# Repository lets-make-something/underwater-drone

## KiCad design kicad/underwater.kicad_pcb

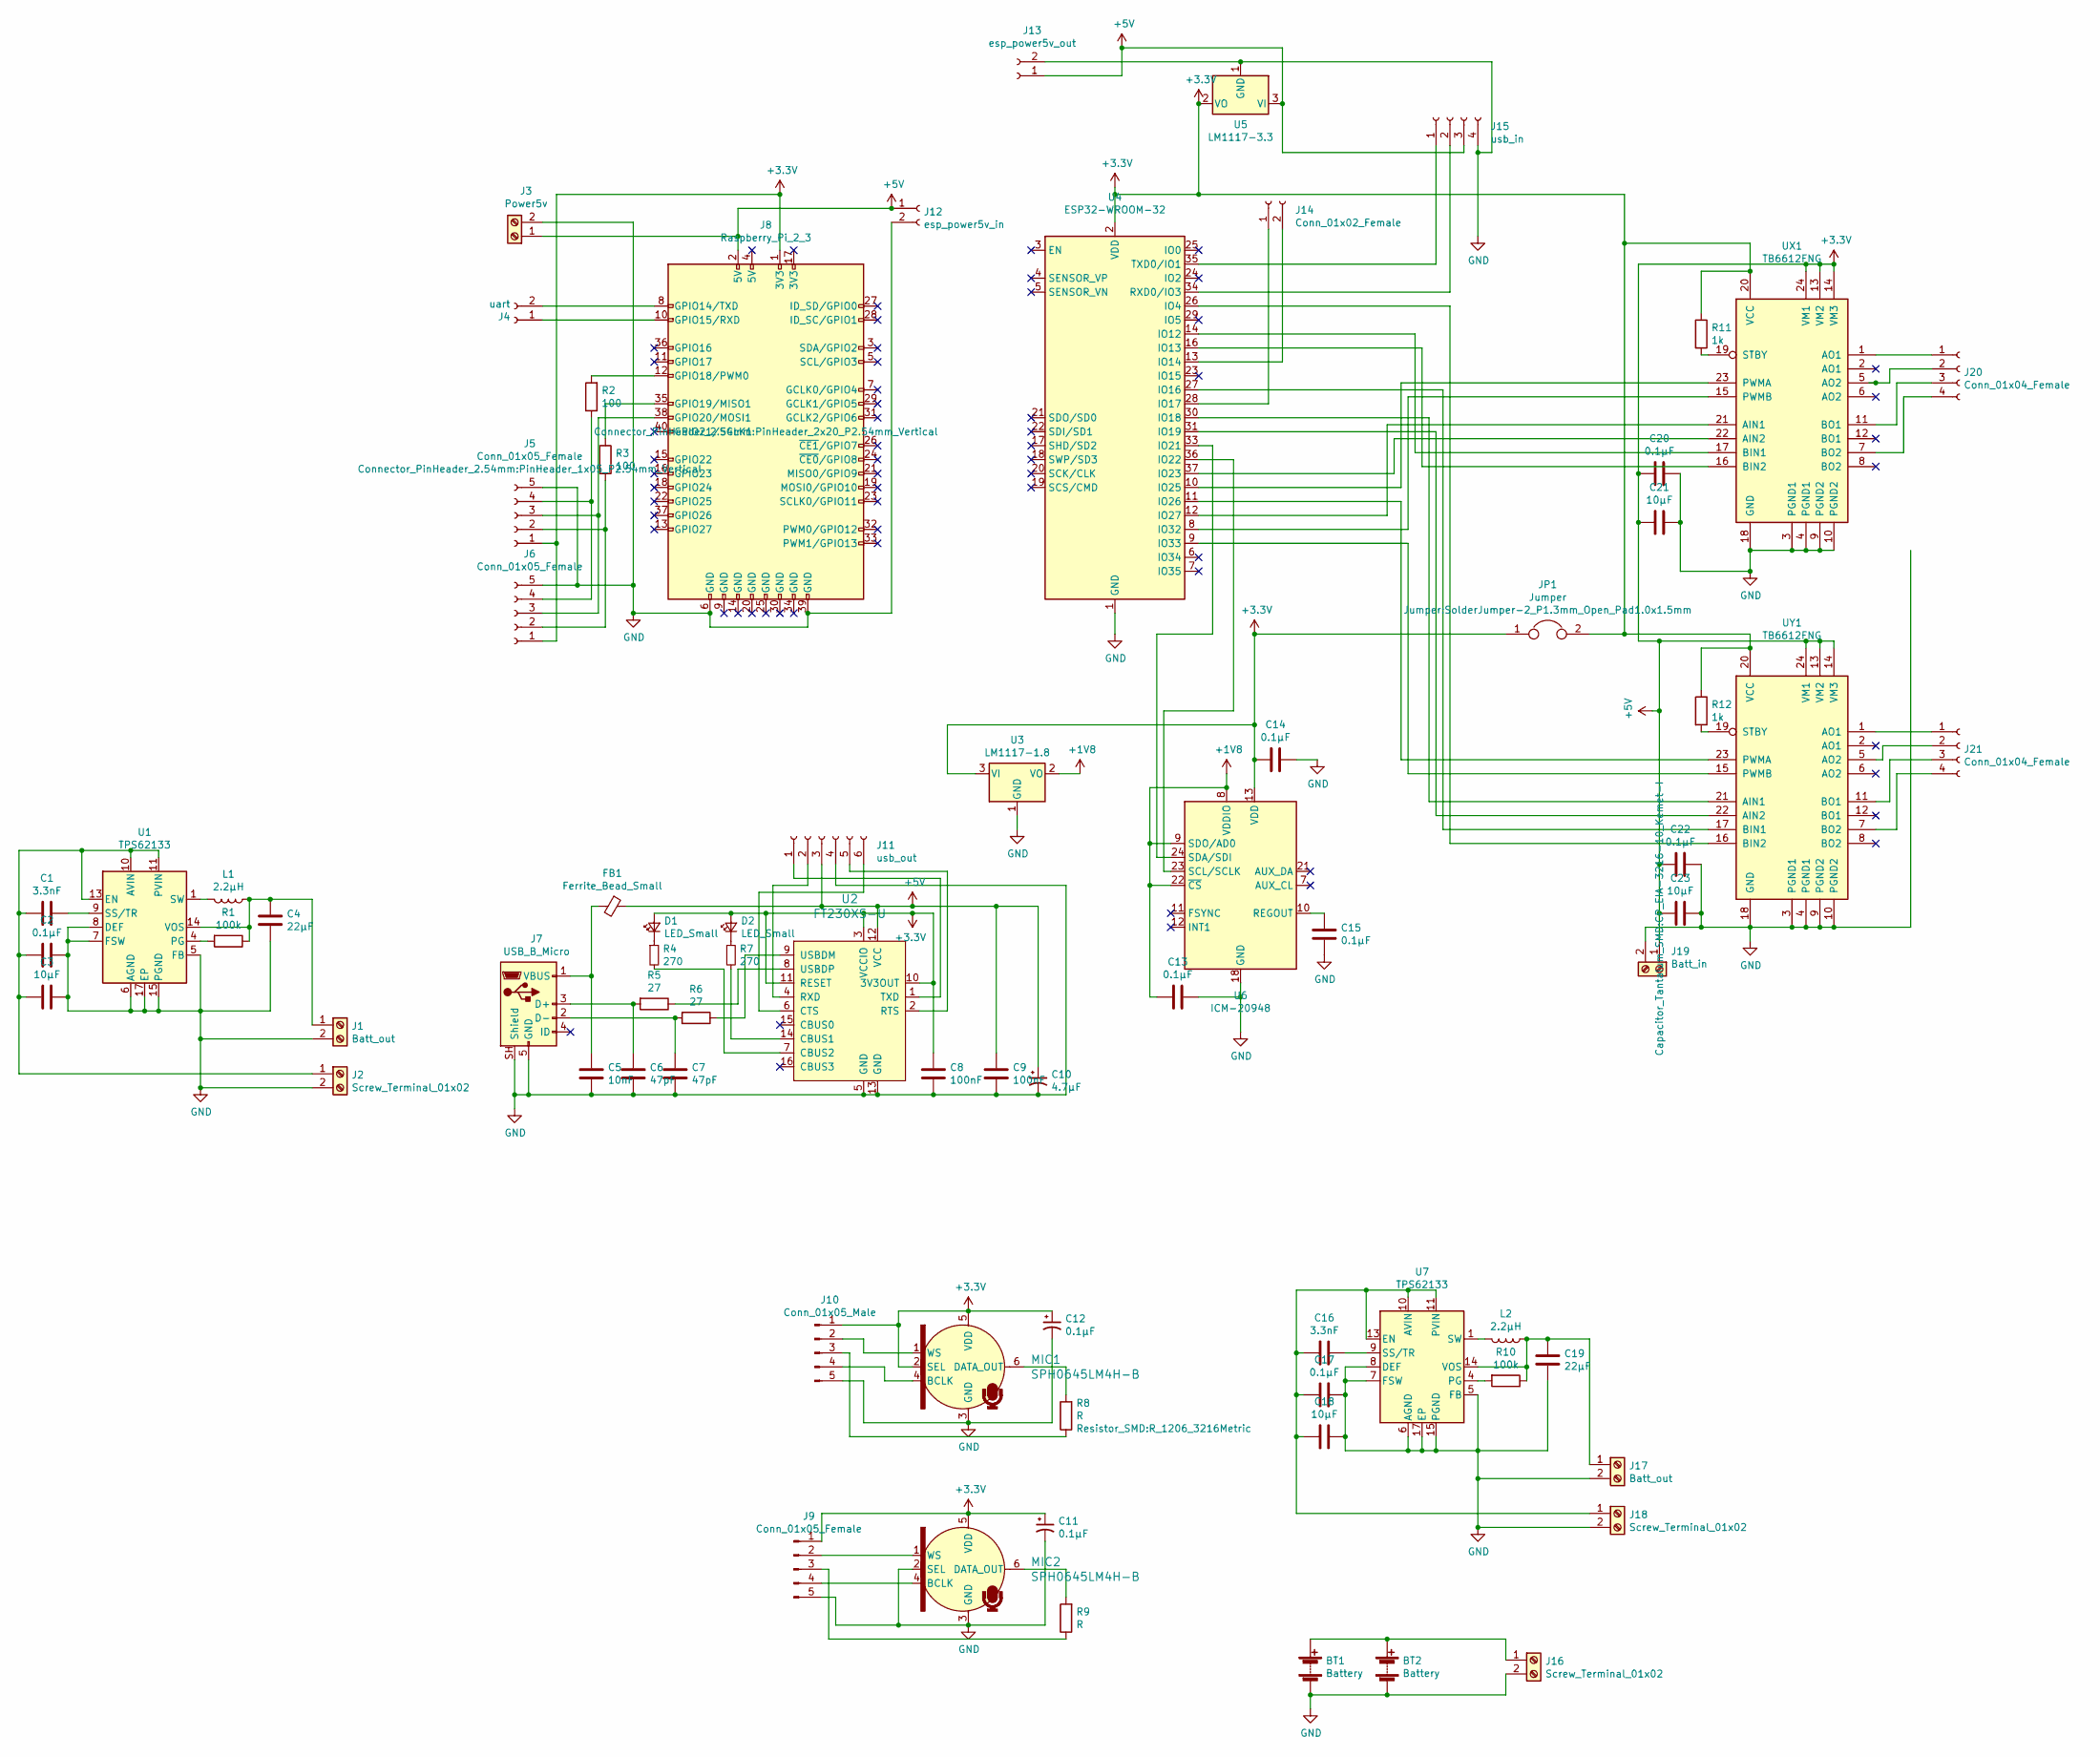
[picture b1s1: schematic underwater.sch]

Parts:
BT1, BT2: Battery; BatteryHolder_Keystone_1042_1x18650
C1, C16: 3.3nF; C_1206_3216Metric
C2, C13, C14, C15, C17, C20, C22: 0.1μF; C_1206_3216Metric
C3, C18, C21, C23: 10μF; CP_EIA-3216-10_Kemet-I
C4, C19: 22μF; CP_EIA-3216-10_Kemet-I
C5: 10nF; C_1206_3216Metric
C6, C7: 47pF; C_1206_3216Metric
C8, C9: 100nF; C_1206_3216Metric
C10: 4.7μF; CP_EIA-3216-10_Kemet-I
C11, C12: 0.1μF; CP_EIA-3216-10_Kemet-I
D1, D2: LED_Small; LED_1206_3216Metric
FB1: Ferrite_Bead_Small; 1206
J1, J17: Batt_out; TerminalBlock_bornier-2_P5.08mm
J2, J16, J18: Screw_Terminal_01x02; TerminalBlock_bornier-2_P5.08mm
J3: Power5v; TerminalBlock_bornier-2_P5.08mm
J4: uart; PinHeader_1x02_P2.54mm_Vertical
J5, J6, J9: Conn_01x05_Female; PinHeader_1x05_P2.54mm_Vertical
J7: USB_B_Micro; USB_Micro_B_Female_10118192
J8: Raspberry_Pi_2_3; PinHeader_2x20_P2.54mm_Vertical
J10: Conn_01x05_Male; PinHeader_1x05_P2.54mm_Vertical
J11: usb_out; PinHeader_1x06_P2.54mm_Vertical
J12: esp_power5v_in; PinHeader_1x02_P2.54mm_Vertical
J13: esp_power5v_out; PinHeader_1x02_P2.54mm_Vertical
J14: Conn_01x02_Female; PinHeader_1x02_P2.54mm_Vertical
J15: usb_in; PinHeader_1x04_P2.54mm_Vertical
J19: Batt_in; TerminalBlock_bornier-2_P5.08mm
J20, J21: Conn_01x04_Female; PinHeader_1x04_P2.54mm_Horizontal
JP1: Jumper; SolderJumper-2_P1.3mm_Open_Pad1.0x1.5mm
L1, L2: 2.2μH; L_1206_3216Metric
MIC1, MIC2: SPH0645LM4H-B; MPN SPH0645LM4H-B; Digi-Key_PN 423-1405-1-ND
R1, R10: 100k; R_1206_3216Metric
R2, R3: 100; R_1206_3216Metric
R4, R7: 270; R_1206_3216Metric
R5, R6: 27; R_1206_3216Metric
R8, R9: R; R_1206_3216Metric
R11, R12: 1k; R_1206_3216Metric
U1, U7: TPS62133; VQFN-16-1EP_3x3mm_P0.5mm_EP1.68x1.68mm_ThermalVias
U2: FT230XS-U; SSOP-16_W3.90mm; MPN FT230XS-U; Digi-Key_PN 768-1154-5-ND
U3: LM1117-1.8; SOT-223-4
U4: ESP32-WROOM-32
U5: LM1117-3.3; SOT-223-4
U6: ICM-20948; InvenSense_QFN-24_3x3mm_P0.4mm
UX1: TB6612FNG; SSOP-24_5.3x8.2mm_P0.65mm
UY1: TB6612FNG; SSOP-24_5.3x8.2mm_P0.65mm

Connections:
+1V8: C13.2, U3.2 (VO), U6.8 (VDDIO), U6.9 (SDO/AD0), U6.22 (~CS)
+3V3: C8.1, C9.1, C10.1, C11.1, C12.1, C14.2, C20.2, C21.2, C22.2, C23.2, D1.2 (A), D2.2 (A), FB1.1, J3.1, J5.1, J6.1, J8.1 (3V3), J8.2 (5V), J9.1, J10.1, J11.3, J12.1, J13.1, J15.3, J19.1, JP1.1, JP1.2, MIC1.2 (SEL), MIC1.5 (VDD), MIC2.5 (VDD), R11.1, R12.1, U2.3 (VCCIO), U2.10 (3V3OUT), U2.11 (RESET), U2.12 (VCC), U3.3 (VI), U4.2 (VDD), U5.2 (VO), U5.3 (VI), U6.13 (VDD), UX1.13 (VM2), UX1.14 (VM3), UX1.20 (VCC), UX1.24 (VM1), UY1.13 (VM2), UY1.14 (VM3), UY1.20 (VCC), UY1.24 (VM1)
GND: BT1.2 (-), BT2.2 (-), C2.2, C3.2, C4.2, C5.2, C6.2, C7.2, C8.2, C9.2, C10.2, C11.2, C12.2, C13.1, C14.1, C15.2, C17.2, C18.2, C19.2, C20.1, C21.1, C22.1, C23.1, J1.2, J2.2, J3.2, J5.5, J6.5, J7.5 (GND), J7.SH (Shield), J8.6 (GND), J8.39 (GND), J9.5, J10.5, J11.4, J12.2, J13.2, J15.4, J16.2, J17.2, J18.2, J19.2, MIC1.3 (GND), MIC2.2 (SEL), MIC2.3 (GND), U1.5 (FB), U1.6 (AGND), U1.7 (FSW), U1.8 (DEF), U1.15 (PGND), U1.16 (PGND), U1.17 (EP), U2.5 (GND), U2.13 (GND), U3.1 (GND), U4.1 (GND), U4.15 (GND), U4.38 (GND), U5.1 (GND), U6.18 (GND), U6.20 (GND), U7.5 (FB), U7.6 (AGND), U7.7 (FSW), U7.8 (DEF), U7.15 (PGND), U7.16 (PGND), U7.17 (EP), UX1.3 (PGND1), UX1.4 (PGND1), UX1.9 (PGND2), UX1.10 (PGND2), UX1.18 (GND), UY1.3 (PGND1), UY1.4 (PGND1), UY1.9 (PGND2), UY1.10 (PGND2), UY1.18 (GND)
unnamed: BT1.1 (+), BT2.1 (+), J16.1
unnamed: C1.1, U1.9 (SS/TR)
unnamed: C1.2, C2.1, C3.1, J2.1, U1.10 (AVIN), U1.11 (PVIN), U1.12 (PVIN), U1.13 (EN)
unnamed: C4.1, J1.1, L1.1, R1.1, U1.14 (VOS)
unnamed: C5.1, FB1.2, J7.1 (VBUS)
unnamed: C6.1, J7.3 (D+), R5.2
unnamed: C7.1, J7.2 (D-), R6.2
unnamed: C15.1, U6.10 (REGOUT)
unnamed: C16.1, U7.9 (SS/TR)
unnamed: C16.2, C17.1, C18.1, J18.1, U7.10 (AVIN), U7.11 (PVIN), U7.12 (PVIN), U7.13 (EN)
unnamed: C19.1, J17.1, L2.1, R10.1, U7.14 (VOS)
unnamed: D1.1 (K), R4.1
unnamed: D2.1 (K), R7.1
unnamed: J4.1, J8.10 (GPIO15/RXD)
unnamed: J4.2, J8.8 (GPIO14/TXD)
unnamed: J5.2, J6.2, R3.2
unnamed: J5.3, J6.3, J8.38 (GPIO20/MOSI1)
unnamed: J5.4, J6.4, R2.1
unnamed: J8.12 (GPIO18/PWM0), R2.2
unnamed: J8.35 (GPIO19/MISO1), R3.1
unnamed: J9.2, MIC2.1 (WS)
unnamed: J9.3, R9.1
unnamed: J9.4, MIC2.4 (BCLK)
unnamed: J10.2, MIC1.1 (WS)
unnamed: J10.3, R8.1
unnamed: J10.4, MIC1.4 (BCLK)
unnamed: J11.1, U2.1 (TXD)
unnamed: J11.2, U2.4 (RXD)
unnamed: J11.5, U2.2 (RTS)
unnamed: J11.6, U2.6 (CTS)
unnamed: J14.1, U4.28 (IO17)
unnamed: J14.2, U4.13 (IO14)
unnamed: J15.1, U4.35 (TXD0/IO1)
unnamed: J15.2, U4.34 (RXD0/IO3)
unnamed: J20.1, UX1.1 (AO1)
unnamed: J20.2, UX1.5 (AO2)
unnamed: J20.3, UX1.11 (BO1)
unnamed: J20.4, UX1.7 (BO2)
unnamed: J21.1, UY1.1 (AO1)
unnamed: J21.2, UY1.5 (AO2)
unnamed: J21.3, UY1.11 (BO1)
unnamed: J21.4, UY1.7 (BO2)
unnamed: L1.2, U1.1 (SW), U1.2 (SW), U1.3 (SW)
unnamed: L2.2, U7.1 (SW), U7.2 (SW), U7.3 (SW)
unnamed: MIC1.6 (DATA_OUT), R8.2
unnamed: MIC2.6 (DATA_OUT), R9.2
unnamed: R1.2, U1.4 (PG)
unnamed: R4.2, U2.7 (CBUS2)
unnamed: R5.1, U2.8 (USBDP)
unnamed: R6.1, U2.9 (USBDM)
unnamed: R7.2, U2.14 (CBUS1)
unnamed: R10.2, U7.4 (PG)
unnamed: R11.2, UX1.19 (STBY)
unnamed: R12.2, UY1.19 (STBY)
unnamed: U4.8 (IO32), UX1.15 (PWMB)
unnamed: U4.9 (IO33), UY1.15 (PWMB)
unnamed: U4.10 (IO25), UX1.23 (PWMA)
unnamed: U4.11 (IO26), UY1.23 (PWMA)
unnamed: U4.12 (IO27), UX1.21 (AIN1)
unnamed: U4.14 (IO12), UX1.17 (BIN1)
unnamed: U4.16 (IO13), UX1.16 (BIN2)
unnamed: U4.26 (IO4), UY1.16 (BIN2)
unnamed: U4.27 (IO16), UY1.17 (BIN1)
unnamed: U4.30 (IO18), UY1.21 (AIN1)
unnamed: U4.31 (IO19), UY1.22 (AIN2)
unnamed: U4.33 (IO21), U6.24 (SDA/SDI)
unnamed: U4.36 (IO22), U6.23 (SCL/SCLK)
unnamed: U4.37 (IO23), UX1.22 (AIN2)

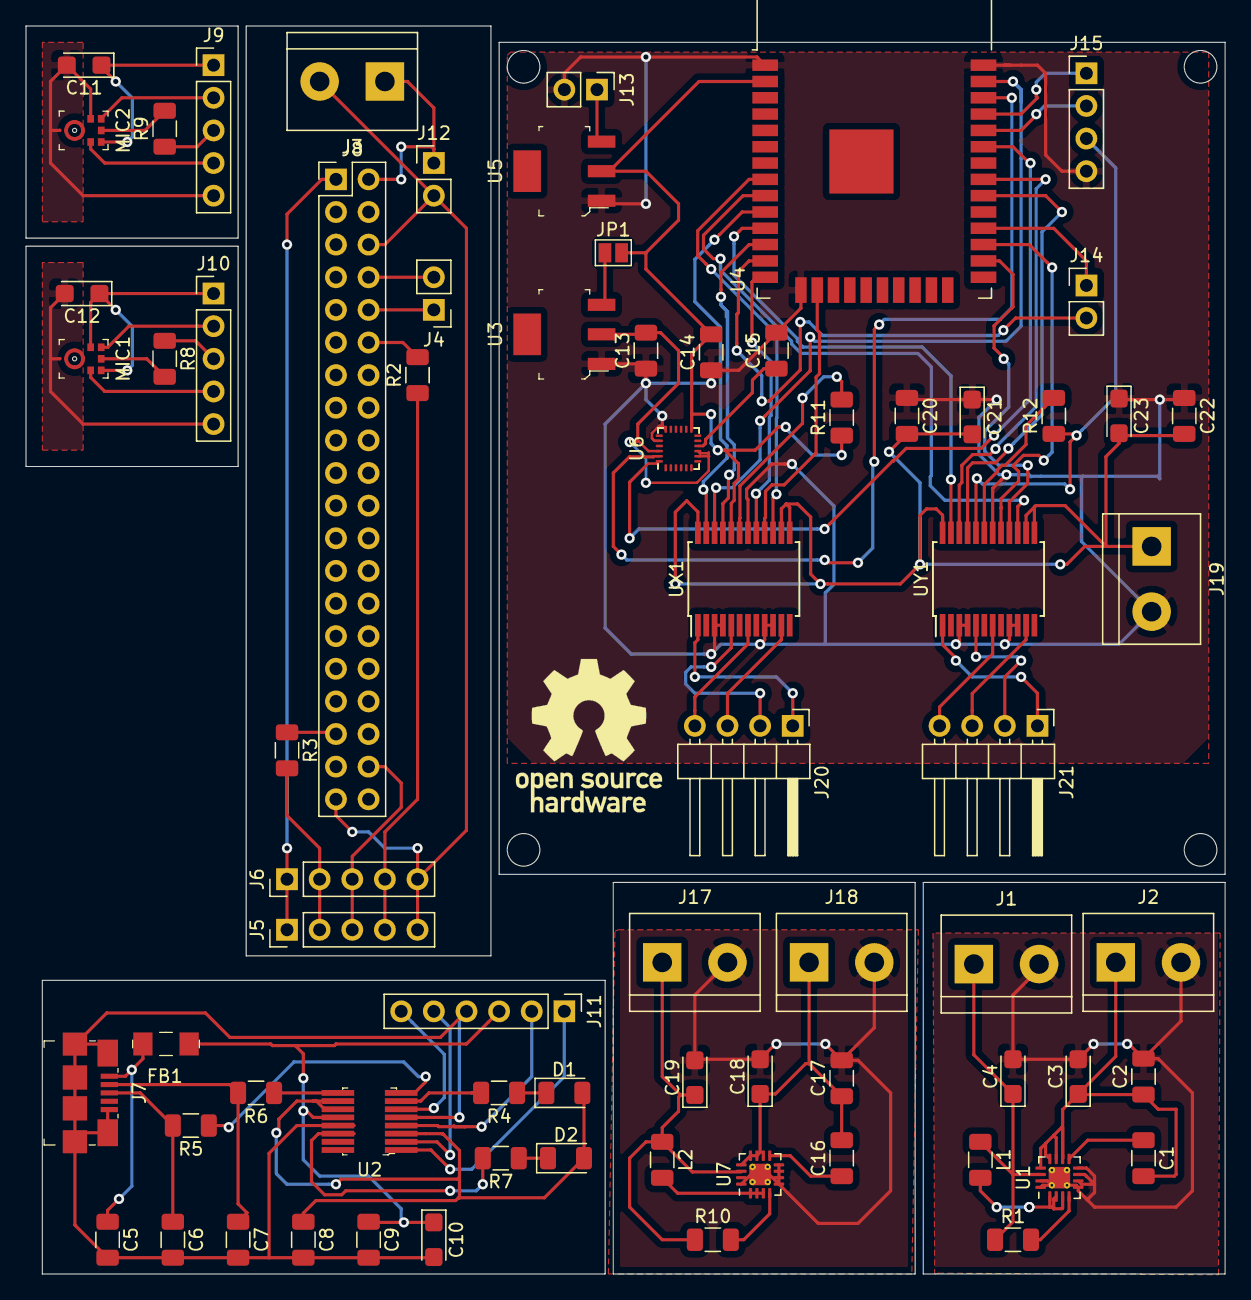
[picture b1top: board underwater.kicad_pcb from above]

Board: 2 copper layers, 93.3 x 97.2 mm, 72 parts (0 on the bottom side), 70 nets.

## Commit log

2019-09-29 Add boot scripts.
2019-09-30 Add feature esp32 underwaterdrone.
2019-10-19 Add models
2019-10-29 Add PCB
2019-11-04 Add kicad net
2019-11-07 format
2019-11-07 Make gbr.
2019-11-07 Fix gbr
